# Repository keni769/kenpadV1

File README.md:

# kenpadV1
kenpadV1 is a macropad with 6 keys and 1 rotary encoder(used for volume up/down and mute). It uses a custom PCB, 3D printed case, and QMK firmware.

## Features

- 6 key + rotary encoder layout
- [3D printed case](/Production)
- [Custom PCB](/PCB)
- [QMK firmware (keys and rotary encode)](/Firmware)

## Schematic

- Switches arranged in a matrix and with 1N4148 diodes.

## PCB

- Features flipped diodes with copper connections on both connections.

## Case

- 4 through holes to secure the case and pcb. 

The shells are attached with the top over the bottom. The shells are secured with 4 M3x16mm screws on the bottom shell.
## BOM
| Item | Qty |
|------|-----|
| Seeed XIAO RP2040 | 1 |
| Through-hole 1N4148 Diode | 6 |
| MX-Style Switch | 6 |
| EC11 Rotary Encoder | 1 |
| White Blank DSA Keycap | 6 |
| M3x16mm Screw | 4 |
| Case | 1 |
| Custom PCB | 1 |

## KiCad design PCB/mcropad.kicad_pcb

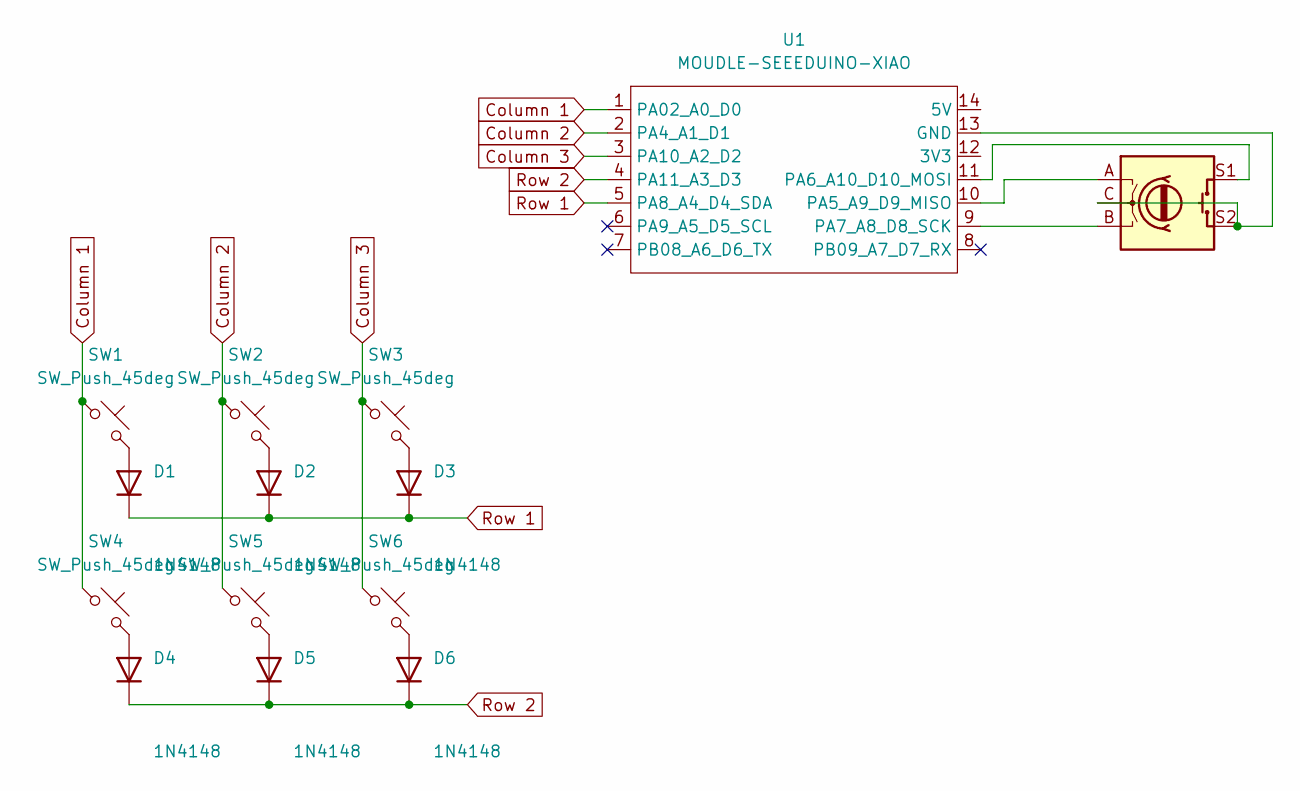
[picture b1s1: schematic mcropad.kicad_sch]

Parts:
D1, D2, D3, D4, D5, D6: 1N4148; D_DO-35_SOD27_P7.62mm_Horizontal
SW1, SW2, SW3, SW4, SW5, SW6: SW_Push_45deg; SW_Cherry_MX_1.00u_PCB
SW7: RotaryEncoder_Switch; RotaryEncoder_Alps_EC11E-Switch_Vertical_H20mm
U1: MOUDLE-SEEEDUINO-XIAO; XIAO-Generic-Hybrid-14P-2.54-21X17.8MM

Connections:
Column 1: SW1.1, SW4.1, U1.1 (PA02_A0_D0)
Column 2: SW2.1, SW5.1, U1.2 (PA4_A1_D1)
Column 3: SW3.1, SW6.1, U1.3 (PA10_A2_D2)
unnamed: D1.2 (A), SW1.2
unnamed: D2.2 (A), SW2.2
unnamed: D3.2 (A), SW3.2
unnamed: D4.2 (A), SW4.2
unnamed: D5.2 (A), SW5.2
unnamed: D6.2 (A), SW6.2
unnamed: SW7.C, SW7.S2, U1.13 (GND)
unnamed: SW7.A, U1.10 (PA5_A9_D9_MISO)
unnamed: SW7.S1, U1.11 (PA6_A10_D10_MOSI)
unnamed: SW7.B, U1.9 (PA7_A8_D8_SCK)
Row 1: D1.1 (K), D2.1 (K), D3.1 (K), U1.5 (PA8_A4_D4_SDA)
Row 2: D4.1 (K), D5.1 (K), D6.1 (K), U1.4 (PA11_A3_D3)

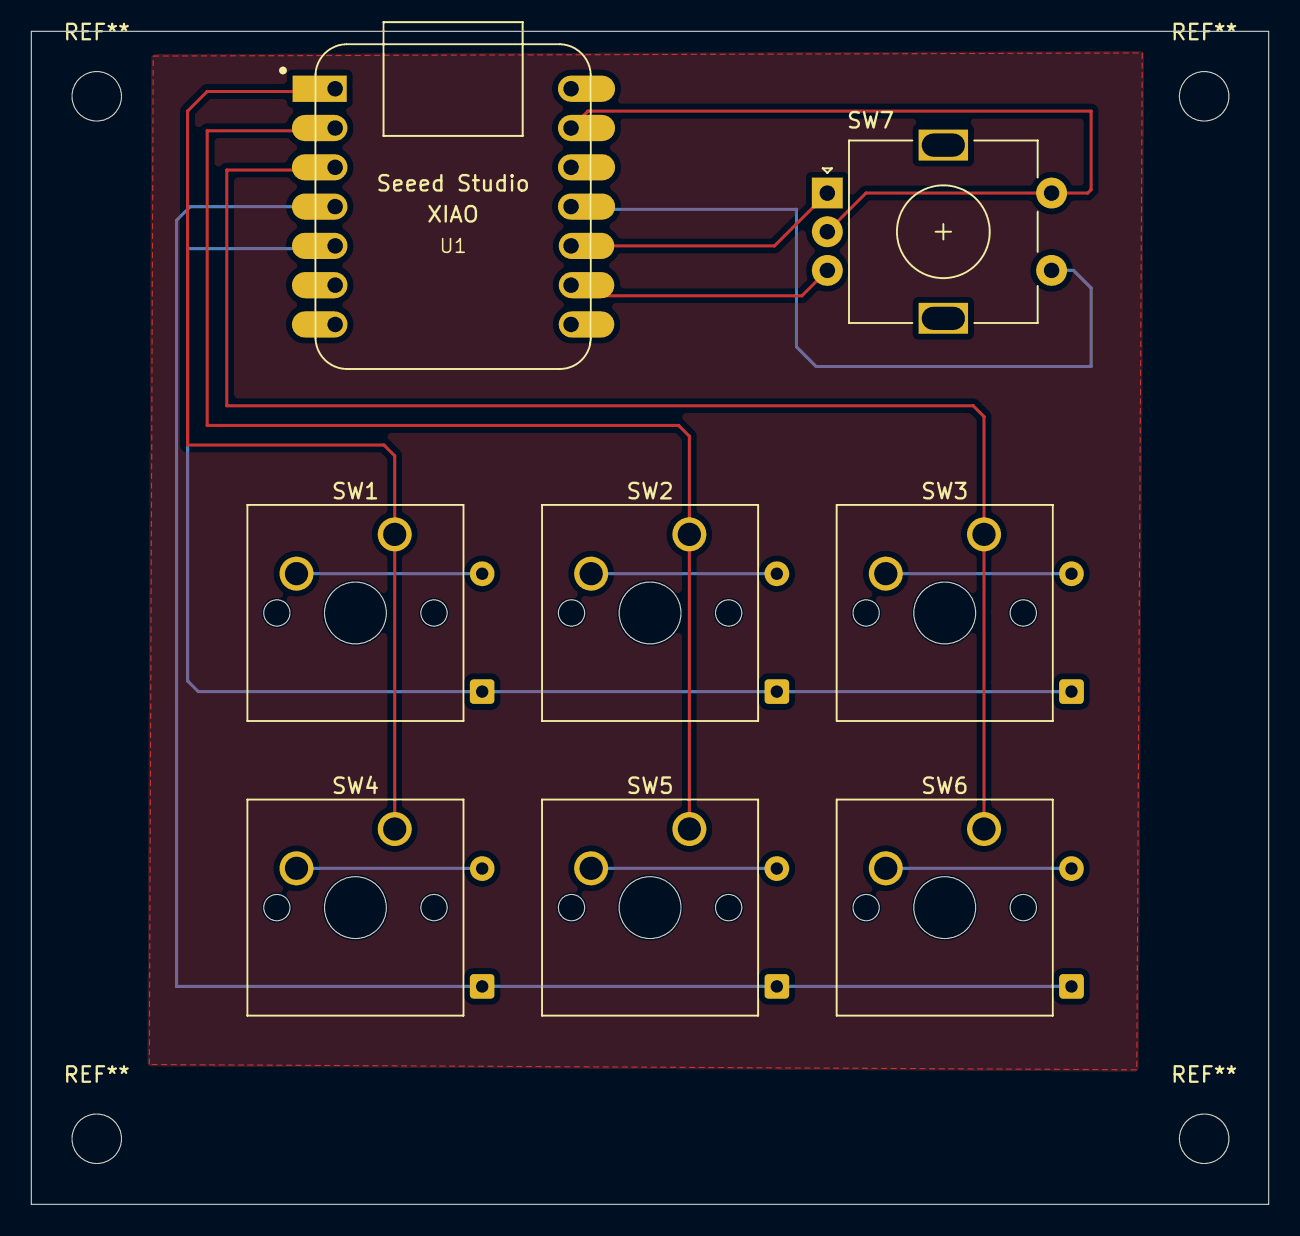
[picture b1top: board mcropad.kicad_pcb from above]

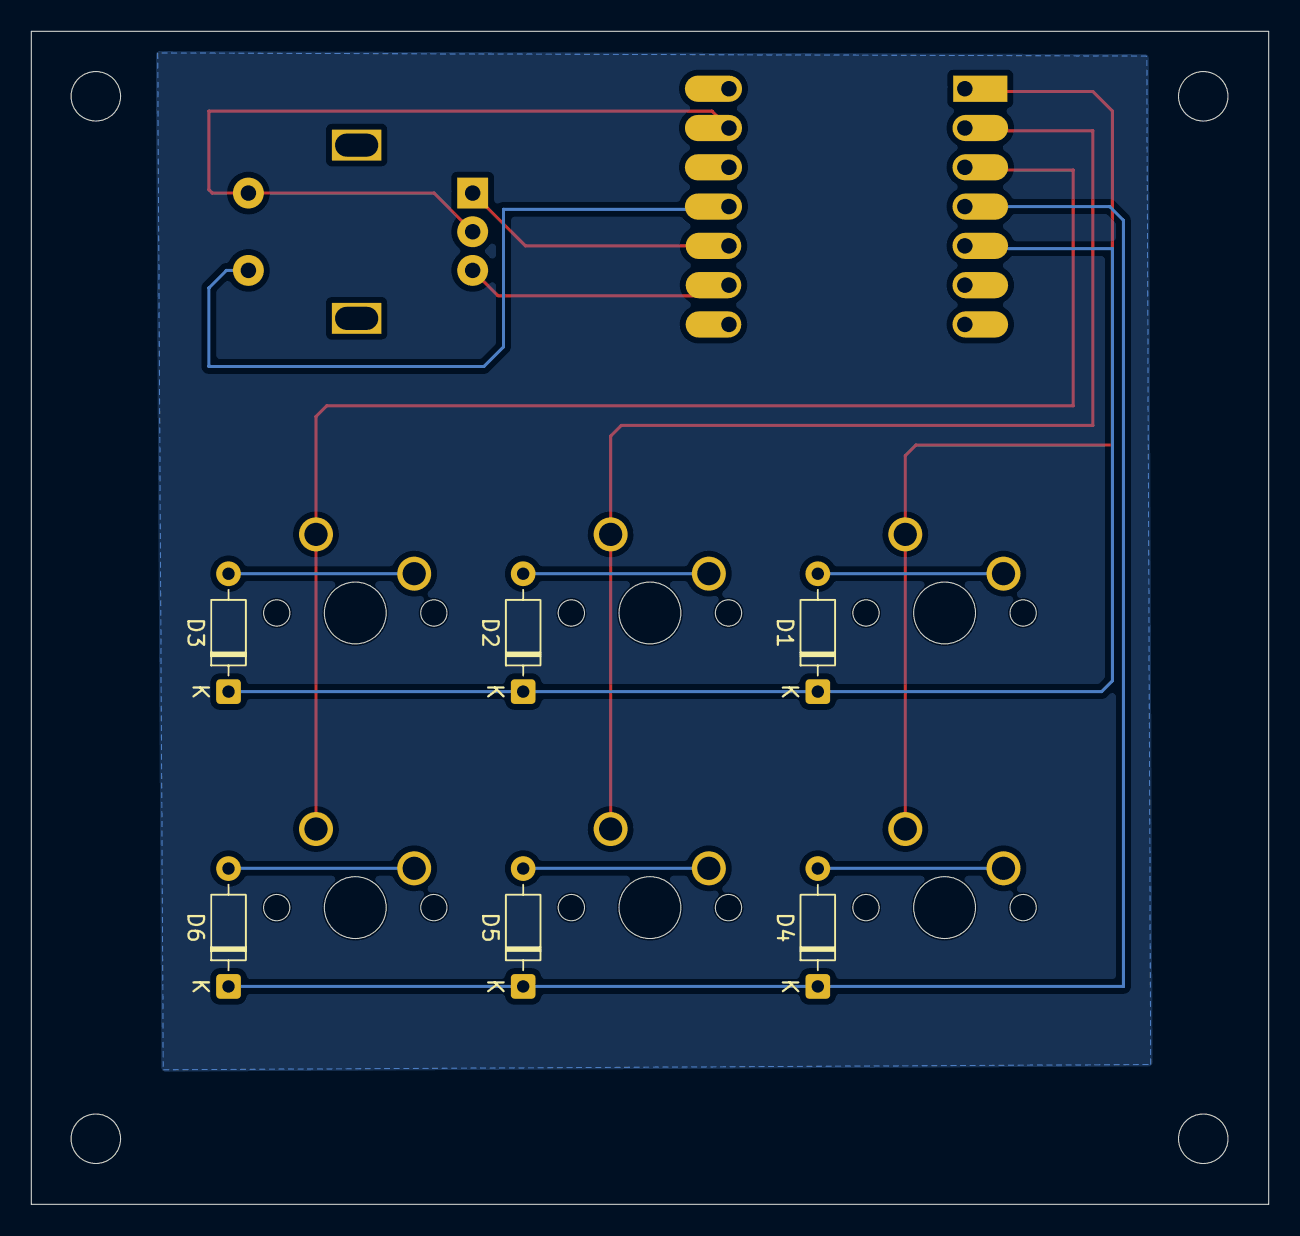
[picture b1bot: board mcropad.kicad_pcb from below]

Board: 2 copper layers, 80.0 x 75.8 mm, 14 parts (6 on the bottom side), 15 nets.
